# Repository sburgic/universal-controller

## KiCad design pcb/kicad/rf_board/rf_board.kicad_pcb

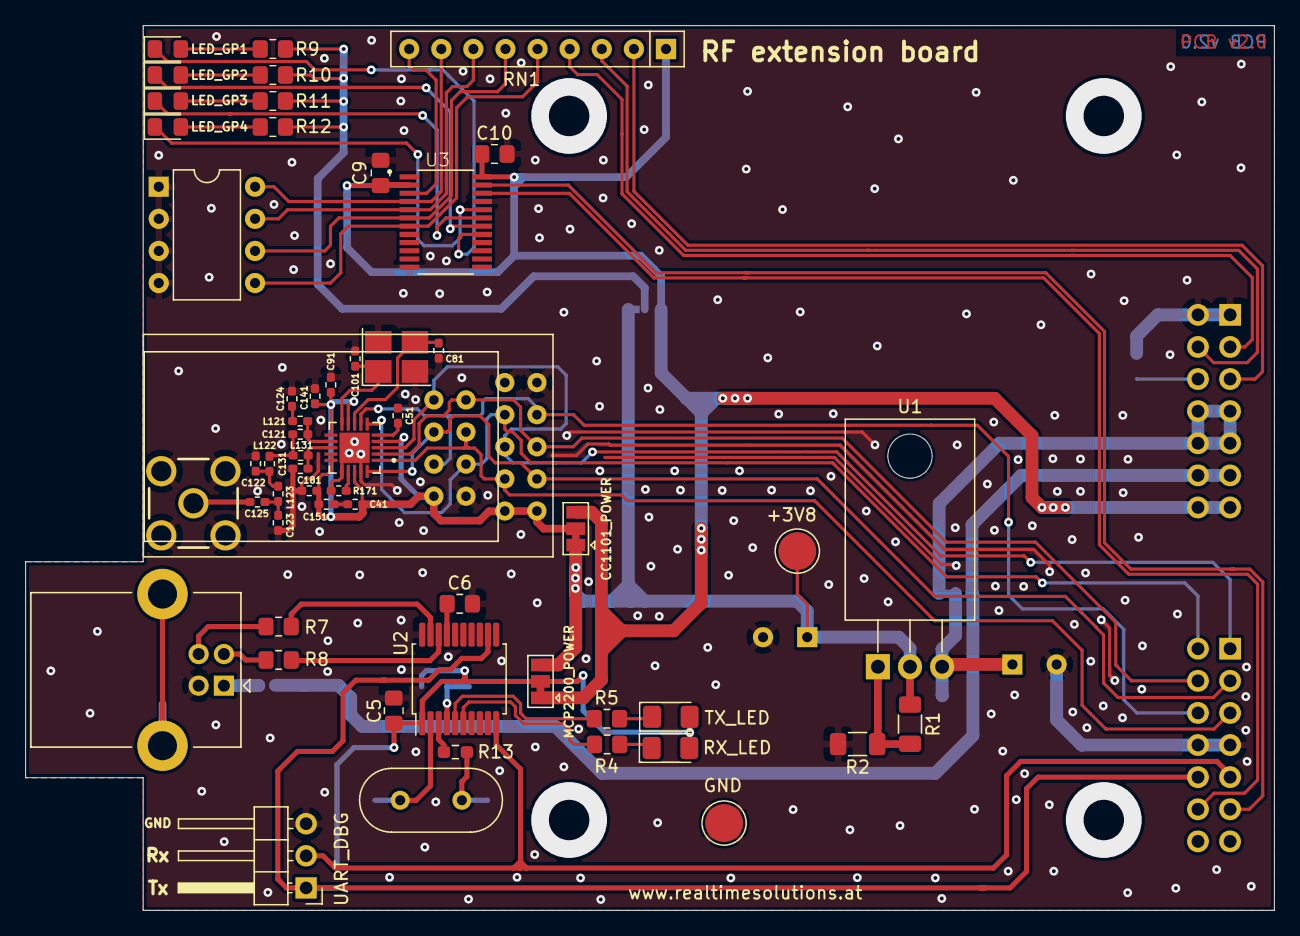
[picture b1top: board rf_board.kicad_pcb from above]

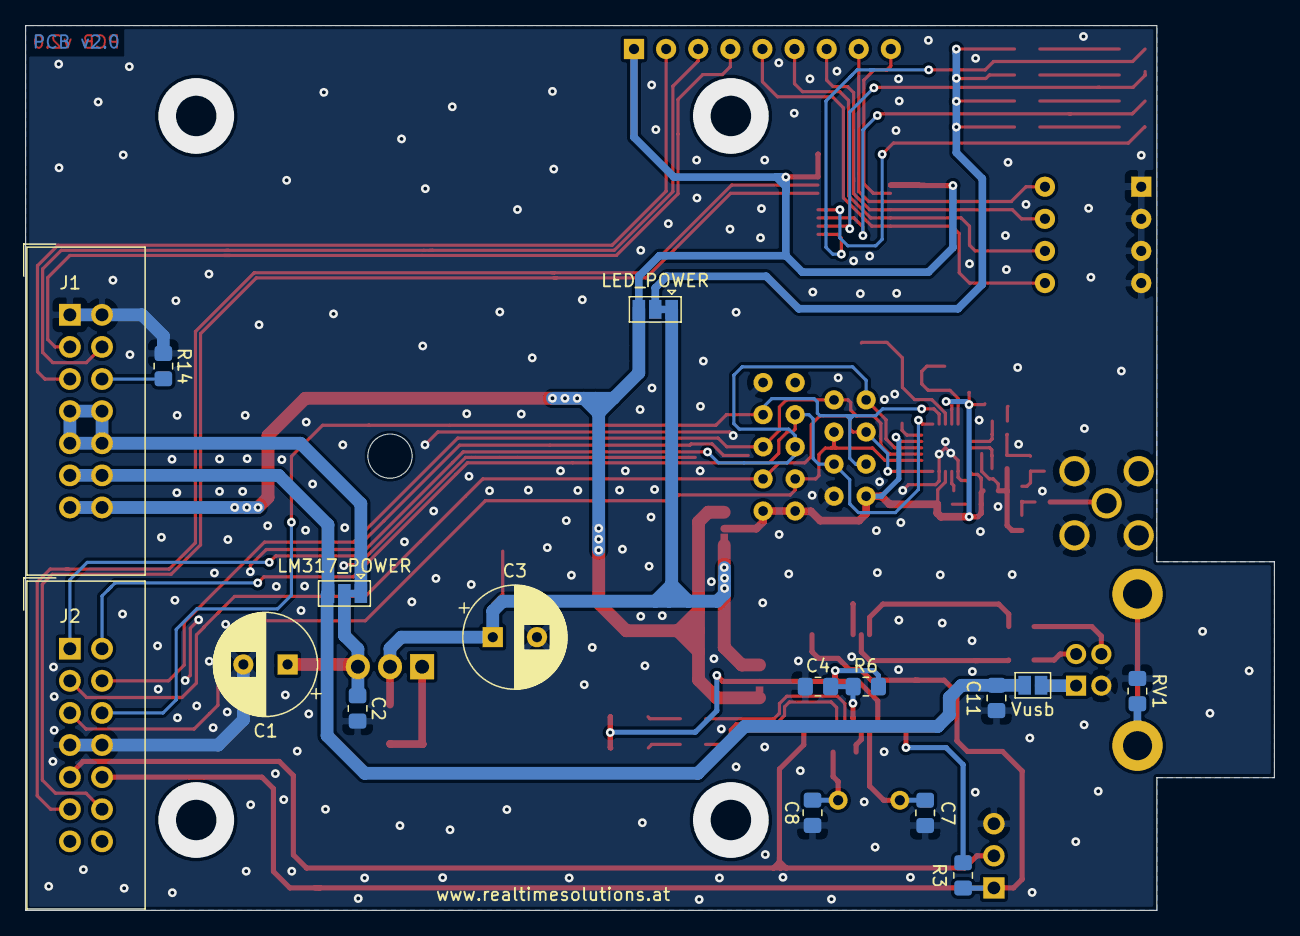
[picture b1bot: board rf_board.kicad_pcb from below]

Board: 2 copper layers, 98.8 x 70.0 mm, 73 parts (16 on the bottom side), 63 nets.

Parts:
C1: 100uF; CP_Radial_D8.0mm_P3.50mm
C2, C4, C5, C6, C9, C10: 100nF; R_0805_2012Metric_Pad1.20x1.40mm_HandSolder
C3: 220uF; CP_Radial_D8.0mm_P3.50mm
C7, C8: 22pF; R_0805_2012Metric_Pad1.20x1.40mm_HandSolder
C11: 10nF; R_0805_2012Metric_Pad1.20x1.40mm_HandSolder
C41, C51, C91: 100nF; R_0402_1005Metric_Pad0.72x0.64mm_HandSolder
C81, C101: 27pF; R_0402_1005Metric_Pad0.72x0.64mm_HandSolder
C121, C131: 3.9pF; R_0402_1005Metric_Pad0.72x0.64mm_HandSolder
C122: 8.2pF; R_0402_1005Metric_Pad0.72x0.64mm_HandSolder
C123: 5.6pF; R_0402_1005Metric_Pad0.72x0.64mm_HandSolder
C124, C125, C151, C181: 220pF; R_0402_1005Metric_Pad0.72x0.64mm_HandSolder
C141: 10nF; R_0402_1005Metric_Pad0.72x0.64mm_HandSolder
D1: RX_LED; LED_1206_3216Metric_Pad1.42x1.75mm_HandSolder
D2: TX_LED; LED_1206_3216Metric_Pad1.42x1.75mm_HandSolder
D3: LED_GP1; LED_0805_2012Metric_Pad1.15x1.40mm_HandSolder
D4: LED_GP2; LED_0805_2012Metric_Pad1.15x1.40mm_HandSolder
D5: LED_GP3; LED_0805_2012Metric_Pad1.15x1.40mm_HandSolder
D6: LED_GP4; LED_0805_2012Metric_Pad1.15x1.40mm_HandSolder
J1: B2B_A; IDC-Header_2x07_P2.54mm_Vertical
J2: B2B_B; IDC-Header_2x07_P2.54mm_Vertical
J3: UART_DBG; PinHeader_1x03_P2.54mm_Horizontal
J4: USB_B; USB_B_Lumberg_2411_02_Horizontal
J5: Antenna 50 Ohm; SAMTEC_SMA-J-P-X-ST-TH1
JP1: MCP2200_POWER; SolderJumper-3_P1.3mm_Bridged12_Pad1.0x1.5mm
JP2: Vusb; SolderJumper-2_P1.3mm_Open_Pad1.0x1.5mm
JP3: LM317_POWER; SolderJumper-3_P1.3mm_Bridged12_Pad1.0x1.5mm
JP4: CC1101_POWER; SolderJumper-3_P1.3mm_Bridged12_Pad1.0x1.5mm
JP5: LED_POWER; SolderJumper-3_P1.3mm_Bridged12_Pad1.0x1.5mm
L121, L123, L131: 27nH; R_0402_1005Metric_Pad0.72x0.64mm_HandSolder
L122: 22nH; R_0402_1005Metric_Pad0.72x0.64mm_HandSolder
R1: 1K2; R_1206_3216Metric_Pad1.30x1.75mm_HandSolder
R2: 2K; R_1206_3216Metric_Pad1.30x1.75mm_HandSolder
R3: 33K; R_0805_2012Metric_Pad1.20x1.40mm_HandSolder
R4, R5: 2K2; R_0805_2012Metric_Pad1.20x1.40mm_HandSolder
R6, R14: 10K; R_0805_2012Metric_Pad1.20x1.40mm_HandSolder
R7, R8: 22R; R_0805_2012Metric_Pad1.20x1.40mm_HandSolder
R9, R10, R11, R12: 220R; R_0805_2012Metric_Pad1.20x1.40mm_HandSolder
R13: 0R; R_0603_1608Metric_Pad0.98x0.95mm_HandSolder
R171: 56K; R_0402_1005Metric_Pad0.72x0.64mm_HandSolder
RN1: R_Network08; R_Array_SIP9
RV1: Varistor; R_0805_2012Metric_Pad1.20x1.40mm_HandSolder
SW1: SW_DIP_x04; DIP-8_W7.62mm
TP1: +3V8; TestPoint_Pad_D3.0mm
TP2: GND; TestPoint_Pad_D3.0mm
U1: LM317_TO-220; TO-220-3_Horizontal_TabDown
U2: MCP2200-I-SS; SSOP-20_5.3x7.2mm_P0.65mm
U3: TCA6416APWR; SOP65P640X120-24N
U4: CC1101_433_MODULE; CC1101_MODULE
U5: CC1101_433_MODULE_SMALL; CC1101_MODULE_SMALL
U6: CC1101RGPR; QFN50P400X400X100-21N
XTAL1: 26Mhz; Crystal_SMD_3225-4Pin_3.2x2.5mm_HandSoldering
XTAL2: 12MHz; Crystal_HC49-U_Vertical

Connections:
+3V3: C9.1, C10.1, J1.13, J1.14, JP1.1, JP4.3, JP5.3, RN1.1, U3.2, U3.24
+3V8: C3.1, JP1.3, JP4.1, JP5.1, R1.1, TP1.1, U1.2
+5V: C11.2, J1.11, J1.12, JP2.1, JP3.3
+12V: J1.7, J1.8, J1.9, J1.10, JP3.1
GND: C1.2, C2.2, C3.2, C4.1, C5.1, C6.2, C7.1, C8.1, C9.2, C10.2, C11.1, C41.1, C51.2, C81.1, C91.1, C101.1, C122.2, C123.2, C124.1, C131.2, C141.1, C151.1, C181.1, J1.1, J1.2, J2.7, J2.8, J3.3, J4.4, J5.2, J5.3, J5.4, J5.5, R2.2, R14.1, R171.1, RV1.2, SW1.1, SW1.2, SW1.3, SW1.4, TP2.1, U2.20, U3.12, U3.21, U4.9, U4.10, U5.1, U6.16, U6.19, U6.21, XTAL1.2, XTAL1.4
HW_ADDR1: J1.6, R14.2
HW_ADDR2: J1.5, RN1.2
HW_ADDR3: J1.4, RN1.3
HW_ADDR4: J1.3, RN1.4
I2C_SCK: J2.12, U3.22
I2C_SDA: J2.11, U3.23
IO1: J2.2, U4.8, U5.3, U6.6
IO2: J2.1, U4.6, U5.8, U6.3
unnamed: C1.1, C2.1, JP3.2, U1.3
unnamed: C4.2, R6.2, U2.4
unnamed: C5.2, D1.2, D2.2, JP1.2, R3.1, R6.1, U2.1
unnamed: C6.1, U2.17
unnamed: C7.2, U2.2, XTAL2.1
unnamed: C8.2, R13.1, XTAL2.2
unnamed: C51.1, U6.5
unnamed: C81.2, U6.8, XTAL1.3
unnamed: C101.2, U6.10, XTAL1.1
unnamed: C121.1, L122.1, L131.2
unnamed: C121.2, L121.2, U6.12
unnamed: C122.1, L122.2, L123.1
unnamed: C123.1, C125.2, L123.2
unnamed: C124.2, L121.1
unnamed: C125.1, J5.1
unnamed: C131.1, L131.1, U6.13
unnamed: C41.2, C91.2, C141.2, C151.2, C181.2, JP4.2, U4.1, U4.2, U5.2, U6.4, U6.9, U6.11, U6.14, U6.15, U6.18
unnamed: D1.1, R4.1
unnamed: D2.1, R5.1
unnamed: D3.1, U3.17
unnamed: D3.2, R9.1
unnamed: D4.1, U3.18
unnamed: D4.2, R10.1
unnamed: D5.1, U3.19
unnamed: D5.2, R11.1
unnamed: D6.1, U3.20
unnamed: D6.2, R12.1
unnamed: J4.1, JP2.2
unnamed: J4.2, R8.1
unnamed: J4.3, R7.1
unnamed: J4.5, RV1.1
unnamed: JP5.2, R9.2, R10.2, R11.2, R12.2
unnamed: R1.2, R2.1, U1.1
unnamed: R4.2, U2.6
unnamed: R5.2, U2.5
unnamed: R7.2, U2.19
unnamed: R8.2, U2.18
unnamed: R13.2, U2.3
unnamed: R171.2, U6.17
unnamed: RN1.5, SW1.5, U3.7
unnamed: RN1.6, SW1.6, U3.6
unnamed: RN1.7, SW1.7, U3.5
unnamed: RN1.8, SW1.8, U3.4
unnamed: RN1.9, U3.3
SPI_CLK: J2.5, U4.4, U5.5, U6.1
SPI_CS: J2.6, U4.7, U5.4, U6.7
SPI_MISO: J2.4, U4.5, U5.7, U6.2
SPI_MOSI: J2.3, U4.3, U5.6, U6.20
UART2_RX: J2.9, J3.2, U2.10
UART2_TX: J2.10, J3.1, R3.2, U2.12

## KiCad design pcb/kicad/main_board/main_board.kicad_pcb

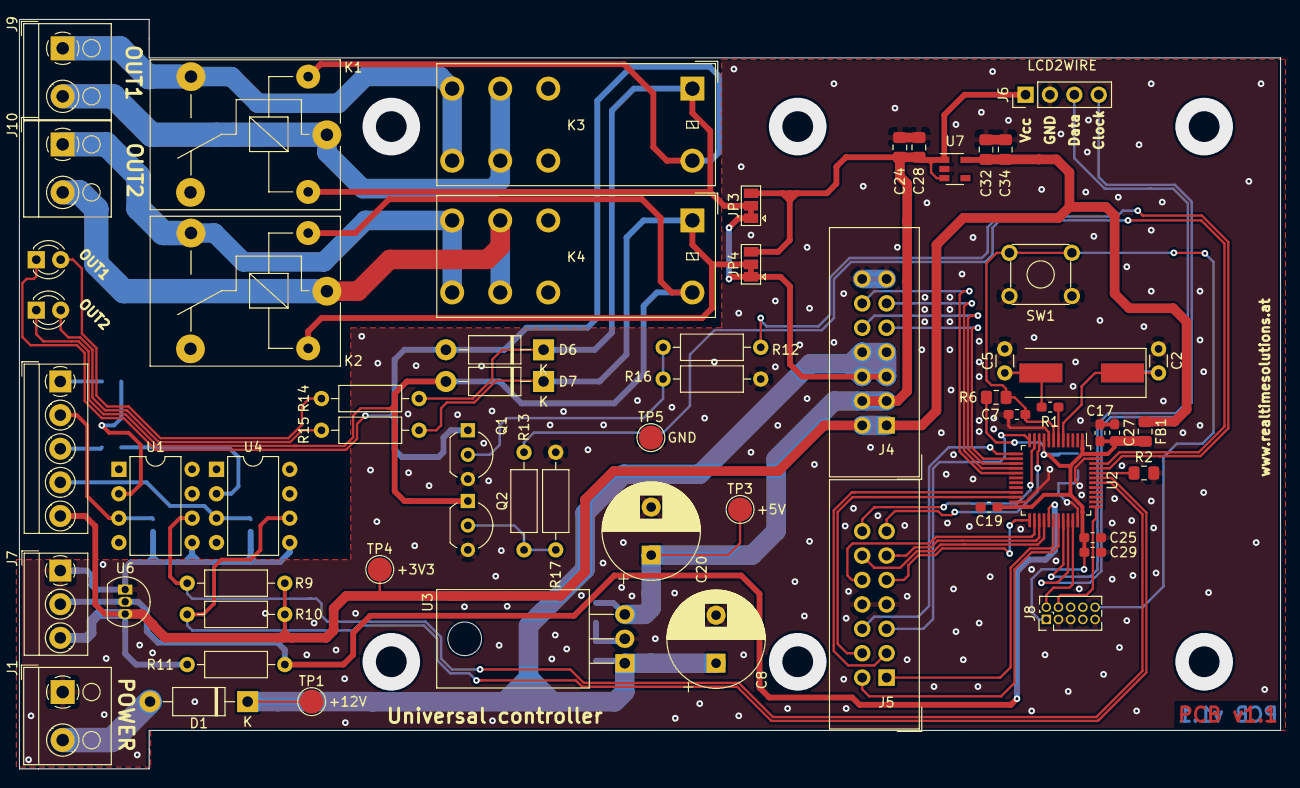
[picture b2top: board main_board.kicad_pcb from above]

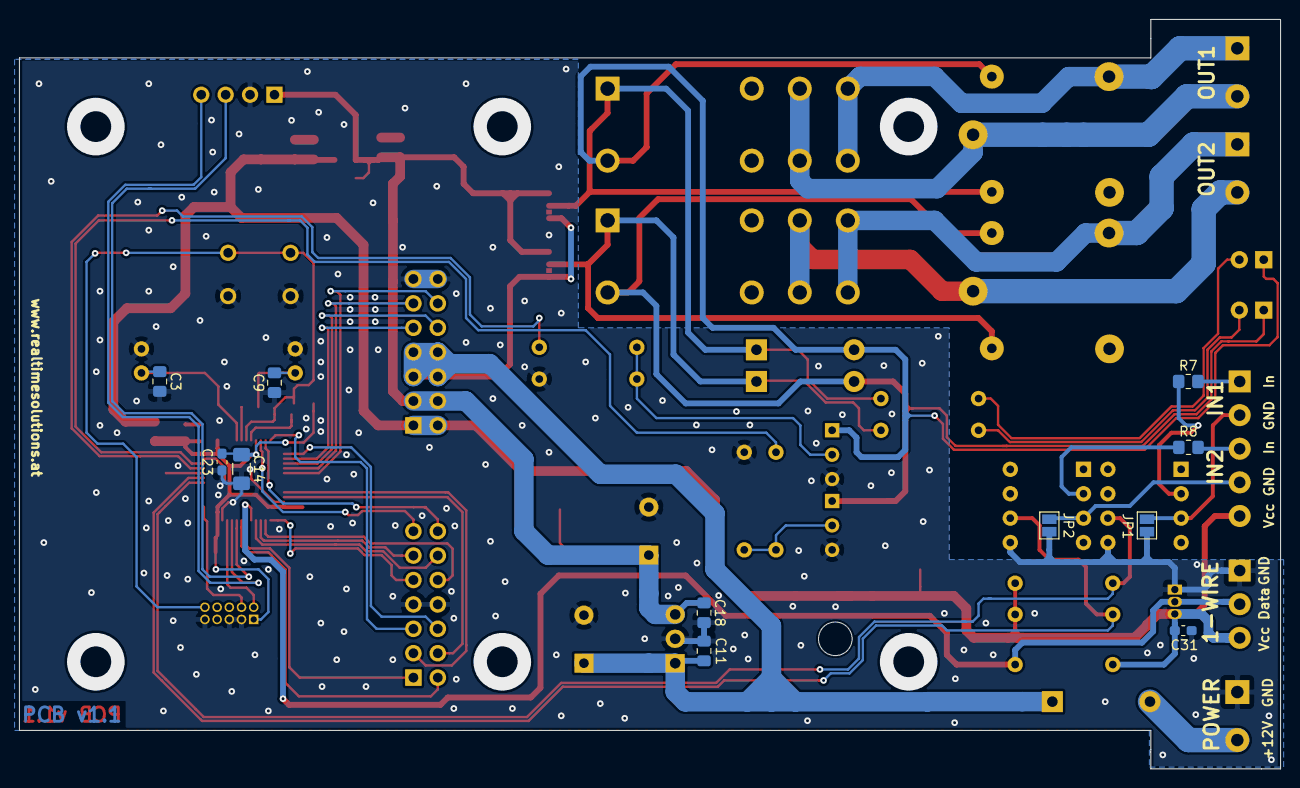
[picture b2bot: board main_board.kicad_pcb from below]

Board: 2 copper layers, 131.2 x 78.0 mm, 72 parts (11 on the bottom side), 54 nets.

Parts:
C2, C5: 22pF; C_Disc_D3.0mm_W1.6mm_P2.50mm
C3, C9: 22pF*; C_0805_2012Metric_Pad1.15x1.40mm_HandSolder
C7, C17, C19, C23, C25, C31: 100nF; C_0603_1608Metric_Pad1.05x0.95mm_HandSolder
C8, C20: 470uF; CP_Radial_D10.0mm_P5.00mm
C11, C18, C28, C32: 100nF; C_0805_2012Metric_Pad1.15x1.40mm_HandSolder
C14: 1uF; C_1206_3216Metric_Pad1.42x1.75mm_HandSolder
C24, C34: 10uF; C_0805_2012Metric_Pad1.15x1.40mm_HandSolder
C27: 10nF; C_0603_1608Metric_Pad1.05x0.95mm_HandSolder
C29: 1nF; C_0603_1608Metric_Pad1.05x0.95mm_HandSolder
D1, D6, D7: 1N4007; D_DO-41_SOD81_P10.16mm_Horizontal
D4, D5: LED; LED_D3.0mm
FB1: MI0805K400R-10; R_0805_2012Metric_Pad1.15x1.40mm_HandSolder
J1: Power; TerminalBlock_RND_205-00001_1x02_P5.00mm_Horizontal
J2: Inputs; TerminalBlock_MetzConnect_Type059_RT06305HBWC_1x05_P3.50mm_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
J4: B2B_A; IDC-Header_2x07_P2.54mm_Vertical
J5: B2B_B; IDC-Header_2x07_P2.54mm_Vertical
J6: LCD2WIRE; PinHeader_1x04_P2.54mm_Vertical
J7: DS18B20; TerminalBlock_MetzConnect_Type059_RT06303HBWC_1x03_P3.50mm_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
J8: PROG; PinHeader_2x05_P1.27mm_Vertical
J9: OUT1; TerminalBlock_RND_205-00001_1x02_P5.00mm_Horizontal
J10: OUT2; TerminalBlock_RND_205-00001_1x02_P5.00mm_Horizontal
JP1, JP2: GND_INT; SolderJumper-2_P1.3mm_Open_Pad1.0x1.5mm
JP3, JP4: Relay_Power; SolderJumper-3_P1.3mm_Bridged12_Pad1.0x1.5mm
K1, K2: FIN36.11.9; Relay_SPDT_SANYOU_SRD_Series_Form_C
K3, K4: G2RL; Relay_DPDT_Omron_G2RL
Q1, Q2: BC337; TO-92_Inline_Wide
R1: 220; R_0603_1608Metric_Pad1.05x0.95mm_HandSolder
R2, R6: 10K; R_0805_2012Metric_Pad1.15x1.40mm_HandSolder
R7, R8: 1K; R_0805_2012Metric_Pad1.20x1.40mm_HandSolder
R9, R10: 1K; R_Axial_DIN0207_L6.3mm_D2.5mm_P10.16mm_Horizontal
R11, R14, R15: 4K7; R_Axial_DIN0207_L6.3mm_D2.5mm_P10.16mm_Horizontal
R12, R13: 2K2; R_Axial_DIN0207_L6.3mm_D2.5mm_P10.16mm_Horizontal
R16, R17: 33K; R_Axial_DIN0207_L6.3mm_D2.5mm_P10.16mm_Horizontal
SW1: RESET; SW_TH_Tactile_Omron_B3F-10xx
TP1: +12V; TestPoint_Pad_D2.5mm
TP3: +5V; TestPoint_Pad_D2.5mm
TP4: +3V3; TestPoint_Pad_D2.5mm
TP5: GND; TestPoint_Pad_D2.5mm
U1, U4: 6N135; DIP-8_W7.62mm
U2: STM32F100C8Tx; LQFP-48_7x7mm_P0.5mm
U3: LM7805; TO-220-3_Horizontal_TabDown
U6: DS18B20; TO-92_Inline
U7: TLV75533PDBV; SOT-23-5
XTAL1: 8,000 MHz; Crystal_SMD_HC49-SD

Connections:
+3V3: C31.2, C32.1, C34.1, FB1.1, J2.5, J4.1, J4.2, J7.3, R9.1, R10.1, R11.2, TP4.1, U6.3, U7.5
+5V: C18.1, C20.1, C24.1, C28.1, J4.3, J4.4, J6.1, JP3.3, JP4.3, TP3.1, U3.3, U7.1, U7.3
+12V: C8.1, C11.1, D1.1, J4.5, J4.6, J4.7, J4.8, JP3.1, JP4.1, TP1.1, U3.1
DS18B20: J7.2, R11.1, U2.29, U6.2
GND: C2.2, C3.2, C5.2, C7.1, C8.2, C9.2, C11.2, C14.2, C17.2, C18.2, C19.2, C20.2, C23.2, C24.2, C25.2, C27.2, C28.2, C29.2, C31.1, C32.2, C34.2, J1.1, J4.13, J4.14, J5.7, J5.8, J6.2, J7.1, J8.3, J8.5, J8.9, JP1.2, JP2.2, Q1.3, Q2.3, R2.2, R16.1, R17.1, SW1.1, SW1.2, TP5.1, U1.5, U2.8, U2.23, U2.35, U2.47, U3.2, U4.5, U6.1, U7.2
HW_ADDR1: J4.9, U2.14
HW_ADDR2: J4.10, U2.15
HW_ADDR3: J4.11, U2.16
HW_ADDR4: J4.12, U2.17
I2C_SCK: J5.3, U2.21
I2C_SDA: J5.4, U2.22
IN1: R9.2, U1.6, U2.42
IN2: R10.2, U2.43, U4.6
IO1: J5.13, U2.10
IO2: J5.14, U2.11
LCD2WIRE_CLK: J6.4, U2.33
LCD2WIRE_DATA: J6.3, U2.32
unnamed: C5.1, C9.1, R1.2, XTAL1.2
unnamed: C14.1, C17.1, C19.1, C23.1, C25.1, C27.1, C29.1, FB1.2, J8.1, R6.2, U2.1, U2.9, U2.24, U2.36, U2.48
unnamed: D1.2, J1.2
unnamed: D4.1, D6.2, K1.2, K3.8, Q1.1
unnamed: D4.2, R14.2
unnamed: D5.1, D7.2, K2.2, K4.8, Q2.1
unnamed: D5.2, R15.2
unnamed: J2.1, R7.2
unnamed: J2.2, JP1.1, U1.3
unnamed: J2.3, R8.2
unnamed: J2.4, JP2.1, U4.3
unnamed: J9.1, K1.3, K3.4, K3.5
unnamed: J9.2, K1.1, K3.3, K3.6
unnamed: J10.1, K2.3, K4.4, K4.5
unnamed: J10.2, K2.1, K4.3, K4.6
unnamed: Q1.2, R12.1, R16.2
unnamed: Q2.2, R13.1, R17.2
unnamed: R2.1, U2.44
unnamed: R7.1, U1.2
unnamed: R8.1, U4.2
OSC_IN: C2.1, C3.1, U2.5, XTAL1.1
OSC_OUT: R1.1, U2.6
OUT1: R12.2, U2.45
OUT2: R13.2, U2.46
RESET: C7.2, J8.10, R6.1, SW1.3, SW1.4, U2.7
RLY1_PWR: D6.1, JP3.2, K1.5, K3.1, R14.1
RLY2_PWR: D7.1, JP4.2, K2.5, K4.1, R15.1
SPI_CLK: J5.10, U2.26
SPI_CS: J5.9, U2.25
SPI_MISO: J5.11, U2.27
SPI_MOSI: J5.12, U2.28
SWCLK: J8.4, U2.37
SWDIO: J8.2, U2.34
UART1_RX: J5.2, U2.31
UART1_TX: J5.1, U2.30
UART2_RX: J5.6, U2.13
UART2_TX: J5.5, U2.12

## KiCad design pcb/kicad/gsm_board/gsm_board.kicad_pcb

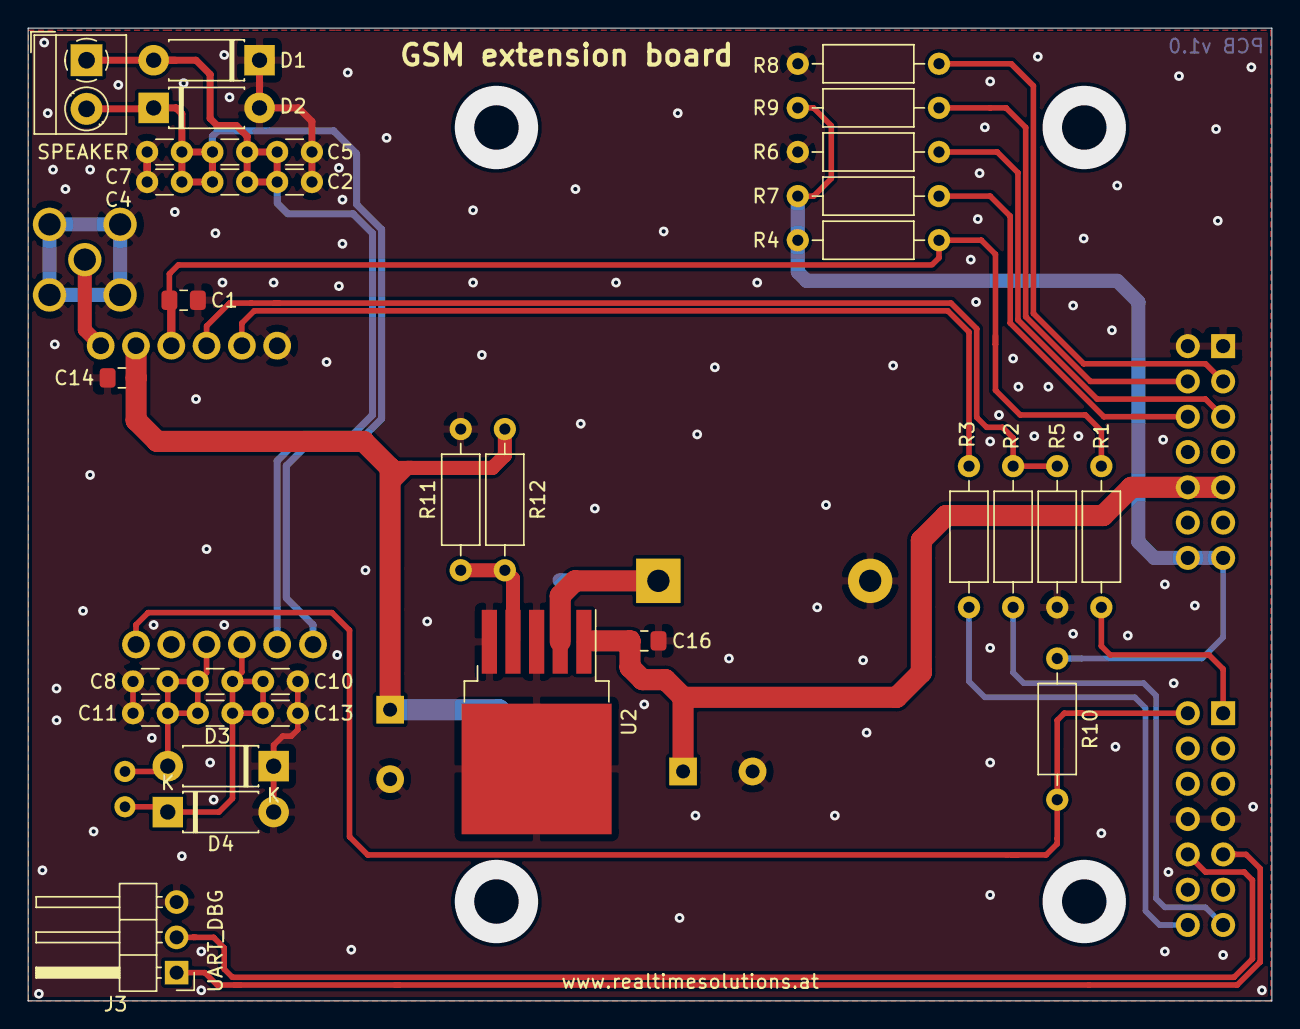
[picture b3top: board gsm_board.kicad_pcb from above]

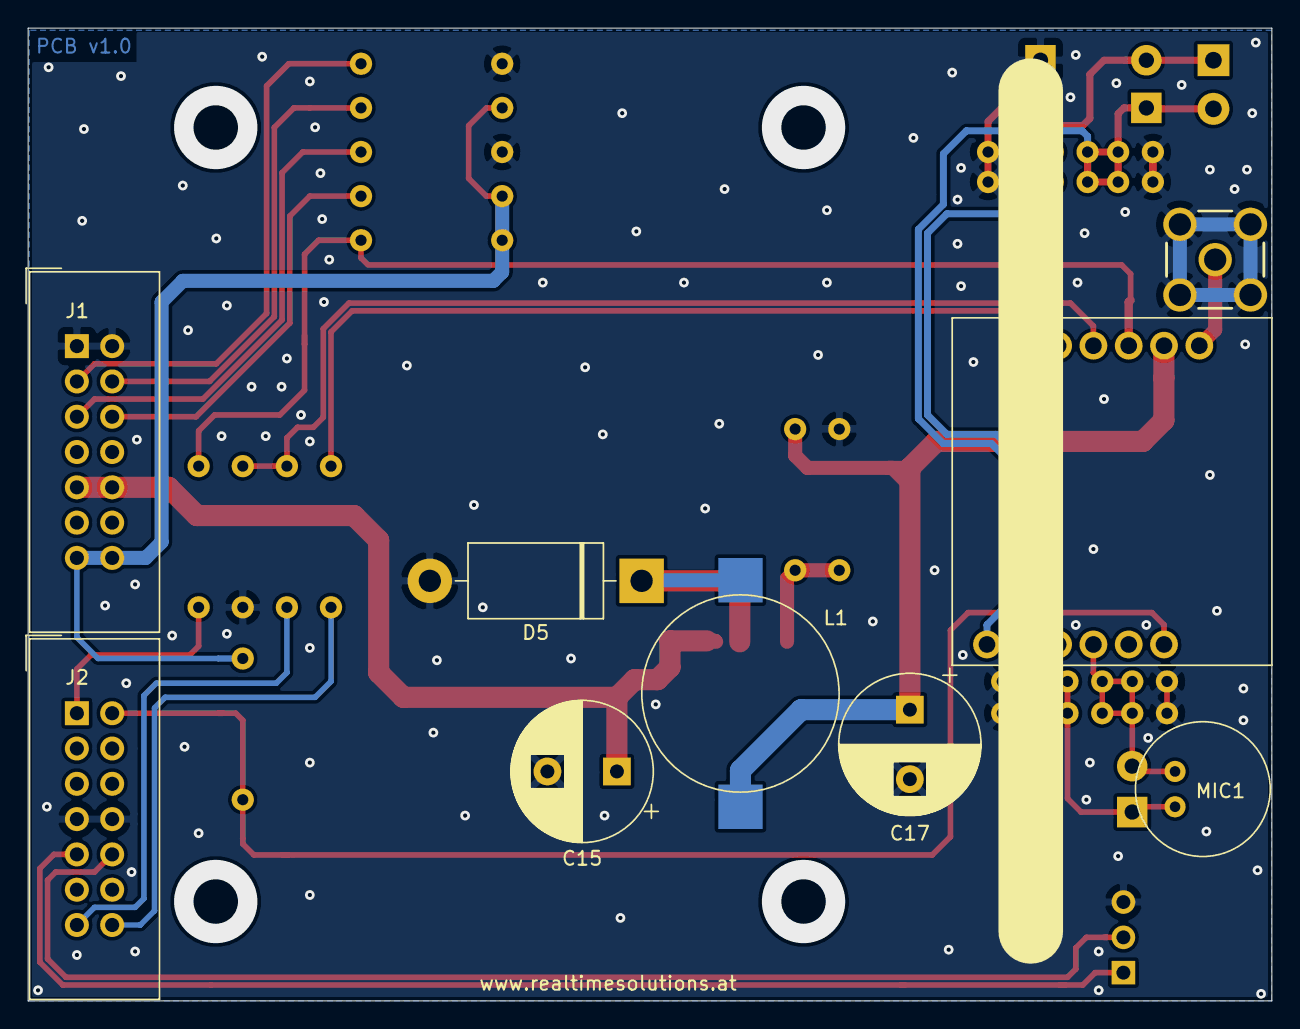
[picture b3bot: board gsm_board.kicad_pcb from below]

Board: 2 copper layers, 89.5 x 70.0 mm, 43 parts (9 on the bottom side), 24 nets.

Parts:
C1, C14, C16: 100nF; C_0805_2012Metric_Pad1.15x1.40mm_HandSolder
C2, C3, C4, C8, C9, C10: 33pF; C_Disc_D3.0mm_W1.6mm_P2.50mm
C5, C6, C7, C11, C12, C13: 10pF; C_Disc_D3.0mm_W1.6mm_P2.50mm
C15: 470uF/25V; CP_Radial_D10.0mm_P5.00mm
C17: 220uF/25V; CP_Radial_D10.0mm_P5.00mm
D1, D2, D3, D4: D_TVS; D_DO-41_SOD81_P7.62mm_Horizontal
D5: 1N5822; D_DO-201AD_P15.24mm_Horizontal
J1: B2B_A; IDC-Header_2x07_P2.54mm_Vertical
J2: B2B_B; IDC-Header_2x07_P2.54mm_Vertical
J3: UART_DBG; PinHeader_1x03_P2.54mm_Horizontal
J4: SPEAKER; TerminalBlock_MetzConnect_Type059_RT06302HBWC_1x02_P3.50mm_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
J5: GSM_ANT; SAMTEC_SMA-J-P-X-ST-TH1
L1: 68uH; L-PISR
MIC1: EMY-9765P
R1: 100; R_Axial_DIN0207_L6.3mm_D2.5mm_P10.16mm_Horizontal
R2, R3, R11: 1K; R_Axial_DIN0207_L6.3mm_D2.5mm_P10.16mm_Horizontal
R4, R6, R7, R8, R9, R10: 10K; R_Axial_DIN0207_L6.3mm_D2.5mm_P10.16mm_Horizontal
R5: 5K6; R_Axial_DIN0207_L6.3mm_D2.5mm_P10.16mm_Horizontal
R12: 2K4; R_Axial_DIN0207_L6.3mm_D2.5mm_P10.16mm_Horizontal
U1: SIM800L; SIM800L_CoreBoard_25x23
U2: LM2596S-ADJ; TO-263-5_TabPin3

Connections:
+3V3: J1.13, J1.14, R4.1, R7.1, R9.1, R10.1
+4V: C14.2, C17.1, L1.2, R12.1, U1.2
+12V: C15.1, C16.1, J1.9, J1.10, U2.1
GND: C1.1, C2.1, C4.2, C5.1, C7.2, C8.1, C10.2, C11.1, C13.2, C14.1, C15.2, C16.2, C17.2, D1.1, D2.2, D3.1, D4.2, D5.2, J1.1, J1.2, J2.7, J2.8, J3.3, J5.2, J5.3, J5.4, J5.5, R5.2, R6.1, R8.1, R11.2, U1.6, U2.3, U2.5
HW_ADDR1: J1.5, R6.2
HW_ADDR2: J1.6, R7.2
HW_ADDR3: J1.3, R8.2
HW_ADDR4: J1.4, R9.2
IO1: J2.1, R1.2
IO2: J2.2, R10.2, U1.12
unnamed: C1.2, R1.1, R4.2, U1.3
unnamed: C2.2, C3.1, C5.2, C6.1, D1.2, J4.1, U1.8
unnamed: C3.2, C4.1, C6.2, C7.1, D2.1, J4.2, U1.7
unnamed: C9.2, C10.1, C12.2, C13.1, D4.1, MIC1.2, U1.9
unnamed: C8.2, C9.1, C11.2, C12.1, D3.2, MIC1.1, U1.10
unnamed: D5.1, L1.1, U2.2
unnamed: J5.1, U1.1
unnamed: R2.1, R5.1, U1.4
unnamed: R3.1, U1.5
unnamed: R11.1, R12.2, U2.4
UART1_RX: J2.14, R3.2
UART1_TX: J2.13, R2.2
UART2_RX: J2.10, J3.2
UART2_TX: J2.9, J3.1

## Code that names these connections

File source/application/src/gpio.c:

/**
 ** Name
 **   gpio.c
 **
 ** Purpose
 **   GPIO routines
 **
 ** Revision
 **   19-Apr-2020 (SSB) [] Initial
 **/

#include "gpio.h"

status_t gpio_init( void )
{
    status_t         ret = STATUS_OK;
    GPIO_InitTypeDef gpio = {0};

    IN1_CLOCK_ENABLE();
    IN2_CLOCK_ENABLE();
    RELAY1_CLOCK_ENABLE();
    RELAY2_CLOCK_ENABLE();
    HW_ADDR1_CLOCK_ENABLE();
    HW_ADDR2_CLOCK_ENABLE();
    HW_ADDR3_CLOCK_ENABLE();
    HW_ADDR4_CLOCK_ENABLE();

    gpio.Pin   = IN1_PIN;
    gpio.Mode  = GPIO_MODE_INPUT;
    gpio.Pull  = GPIO_NOPULL;
    gpio.Speed = GPIO_SPEED_FREQ_LOW;
    HAL_GPIO_Init( IN1_PORT, &gpio );

    gpio.Pin = IN2_PIN;
    HAL_GPIO_Init( IN2_PORT, &gpio );

    gpio.Pull = GPIO_PULLDOWN;
    gpio.Pin  = HW_ADDR1_PIN;
    HAL_GPIO_Init( HW_ADDR1_PORT, &gpio );

    gpio.Pin = HW_ADDR2_PIN;
    HAL_GPIO_Init( HW_ADDR2_PORT, &gpio );

    gpio.Pin = HW_ADDR3_PIN;
    HAL_GPIO_Init( HW_ADDR3_PORT, &gpio );

    gpio.Pin = HW_ADDR4_PIN;
    HAL_GPIO_Init( HW_ADDR4_PORT, &gpio );

    gpio.Pin  = RELAY1_PIN;
    gpio.Mode = GPIO_MODE_OUTPUT_PP;
    HAL_GPIO_Init( RELAY1_PORT, &gpio );

    gpio.Pin = RELAY2_PIN;
    HAL_GPIO_Init( RELAY2_PORT, &gpio );

    return ret;
}

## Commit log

2020-12-19 add .gitignore
2020-12-19 add PCBs
2020-12-19 add initial source code
2021-01-06 finalize bluetooth communication
2021-01-16 fix bluetooth timeout values
2021-01-22 add cc1101; remove gsm support
2021-01-24 add suport for iar compiler
2021-02-25 Add ver.1.0.0 (bluetooth only)
2021-02-25 Add GSM support
2021-02-25 Remove unused files
2021-02-26 Fix temperature output strings
2021-03-09 Add temperature hysteresis
2021-04-18 Add main board PCB ver.1.1
2021-04-18 Add RF board PCB ver.2.0
2021-04-21 Add doc folder
2021-07-24 Fix bug in Bluetooth initialization
